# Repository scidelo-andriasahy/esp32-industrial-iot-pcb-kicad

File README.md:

# Industrial ESP32 IoT Hardware & KiCad PCB Ecosystem (Fortico R&D)

> **Author:** Tsikomia Scidelo ANDRIASAHY — Embedded Hardware R&D at [Fortico](https://sitewebfortico.vercel.app/fr)  
> **Live Project Showcase:** [https://scidelo-andriasahy.github.io/?project=5](https://scidelo-andriasahy.github.io/?project=5)

## Four Industrial Embedded Systems Included
1. **SMART_COUNT Industrial Counter PCB:** `ESP32` driving 4 cascaded `74HC595` shift registers + 4 seven-segment displays, ultrasonic object detection, and MQTT reporting.
2. **Automated Smart Incubator PCB:** MOSFET PID thermal loop, DHT22 hygrometry, NEMA 17 egg turning (`DRV8825`), `DS3231` RTC, and 12V/Battery automatic failover.
3. **Multi-Module Fleet Telematics IoT Box:** `ESP32` + `SIM7600` 4G LTE modem + NEO-6M GPS + RFID driver authentication + offline microSD buffering + security relay.
4. **Remote Operator HMI Terminal:** SSD1306 OLED, rotary encoder, and bidirectional `ESP-NOW` / `MQTT` telemetry for power converters.

## Repository Structure
```text
├── hardware/
│   ├── smart_count_kicad/      # Complete KiCad schematic & PCB layout for SMART_COUNT
│   └── smart_incubator_kicad/  # Complete KiCad schematic & PCB layout for Smart Incubator
├── docs/                       # ERC-verified PDF schematics & full functional/firmware specs
└── media/                      # 3D PCB renders & schematic previews
```

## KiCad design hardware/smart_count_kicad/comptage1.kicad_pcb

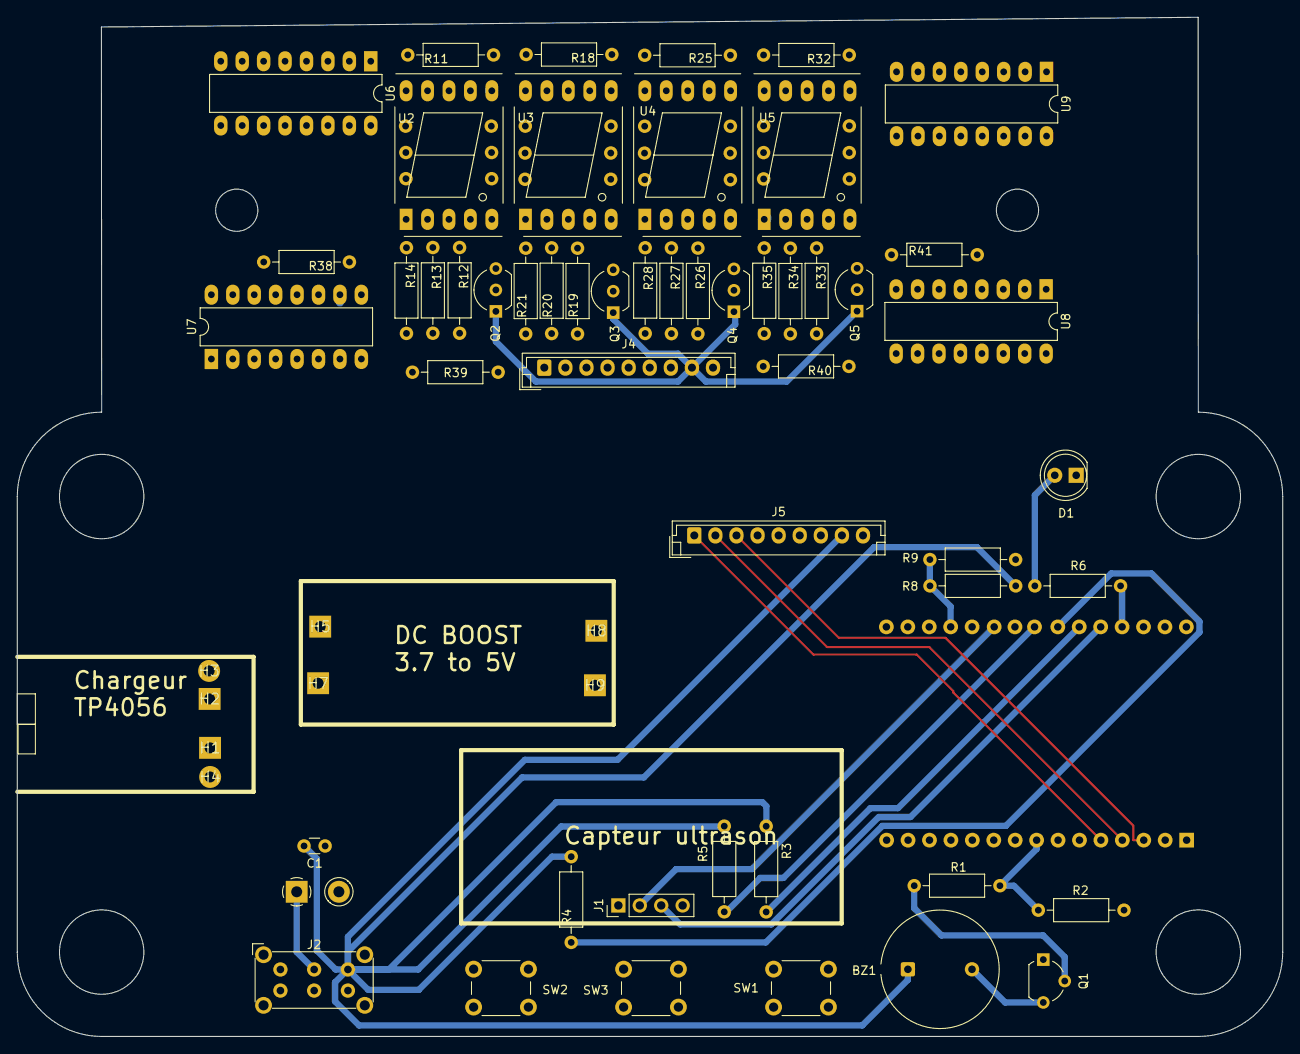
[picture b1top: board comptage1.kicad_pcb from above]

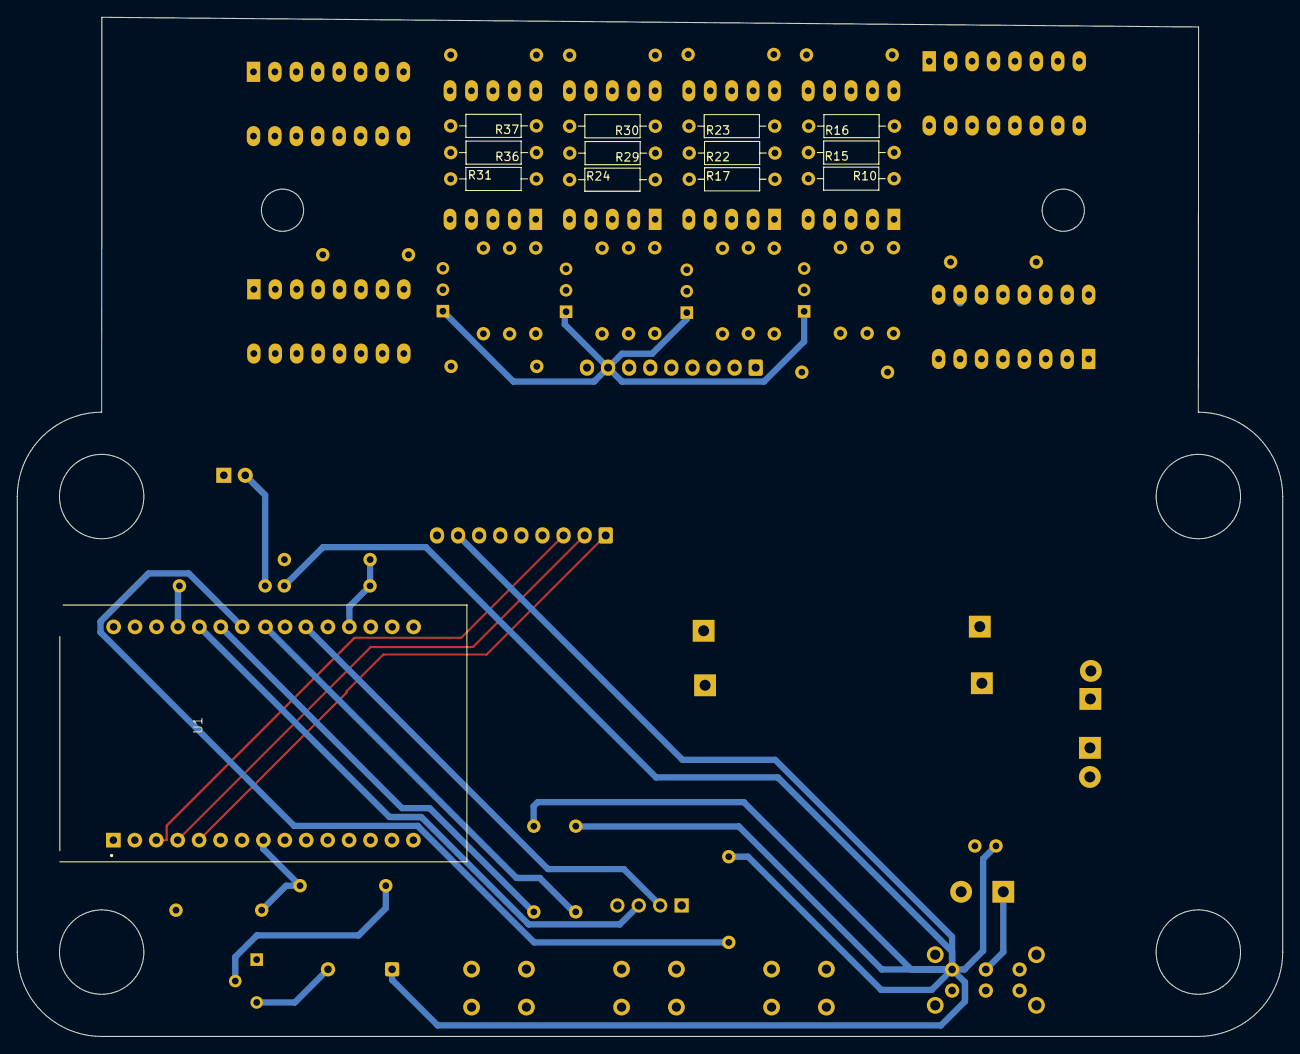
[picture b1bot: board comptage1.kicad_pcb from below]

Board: 2 copper layers, 150.0 x 120.8 mm, 73 parts (13 on the bottom side), 101 nets.

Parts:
BZ1: Buzzer; Indicator_PUI_AI-1440-TWT-24V-2-R
C1: 100nf; C_Disc_D3.0mm_W1.6mm_P2.50mm
D1: Alim; LED_D5.0mm
H1, H2, H3, H4, H5, H7, H8, H9: (no value)
J1: Conn_01x06; PinHeader_1x04_P2.54mm_Vertical
J2: Intérrupteur; SW_E-Switch_EG2219_DPDT_Angled
J3: Source; TerminalBlock_Phoenix_MKDS-1,5-2_1x02_P5.00mm_Horizontal
J4, J5: Conn_01x04; JST_EH_B9B-EH-A_1x09_P2.50mm_Vertical
Q1: 2SC1941; TO-92L_Wide
Q2, Q3, Q4, Q5: PNP; TO-92_Inline_Wide
R1, R38, R39, R40, R41: 330; R_Axial_DIN0207_L6.3mm_D2.5mm_P10.16mm_Horizontal
R2: 10ΚΩ; R_Axial_DIN0207_L6.3mm_D2.5mm_P10.16mm_Horizontal
R3, R4, R5: 10K; R_Axial_DIN0207_L6.3mm_D2.5mm_P10.16mm_Horizontal
R6, R10, R11, R12, R13, R14, R15, R16, R17, R18, R19, R20, R21, R22, R23, R24, R25, R26, R27, R28, R29, R30, R31, R32, R33, R34, R35, R36, R37: 32K; R_Axial_DIN0207_L6.3mm_D2.5mm_P10.16mm_Horizontal
R8, R9: 32KΩ; R_Axial_DIN0207_L6.3mm_D2.5mm_P10.16mm_Horizontal
SW1, SW2, SW3: SW_MEC_5G; SW_PUSH_6mm_H8mm
U1: ESP32-DEVKIT-V1; ESP32 DEVKIT V1
U2: Ecran 1; 7SegmentLED_LTS6760_LTS6780
U3: Ecran 2; 7SegmentLED_LTS6760_LTS6780
U4: Ecran 3; 7SegmentLED_LTS6760_LTS6780
U5: Ecran 4; 7SegmentLED_LTS6760_LTS6780
U6, U7, U8, U9: 74HC595; DIP-16_W7.62mm_LongPads

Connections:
/A1-: R10.2, U6.15 (QA)
/A2-: R17.2, U7.15 (QA)
/A3-: R24.2, U8.15 (QA)
/A4-: R31.2, U9.15 (QA)
/B1-: R11.2, U6.1 (QB)
/B2-: R18.2, U7.1 (QB)
/B3-: R25.2, U8.1 (QB)
/B4-: R32.2, U9.1 (QB)
/C1-: R12.2, U6.2 (QC)
/C2-: R19.2, U7.2 (QC)
/C3-: R26.2, U8.2 (QC)
/C4-: R33.2, U9.2 (QC)
/D1-: R13.2, U6.3 (QD)
/D2: J5.2, U1.4 (D2)
/D2-: R20.2, U7.3 (QD)
/D3-: R27.2, U8.3 (QD)
/D4: J5.1, U1.5 (D4)
/D4-: R34.2, U9.3 (QD)
/D5: R1.2, R2.2, U1.8 (D5)
/D12: R6.2, U1.27 (D12)
/D13: J5.4, U1.28 (D13)
/D14: J1.3, U1.26 (D14)
/D15: J5.3, U1.3 (D15)
/D21: J5.7, U1.11 (D21)
/D22: J5.6, U1.14 (D22)
/D23: J5.5, U1.15 (D23)
/D25: R5.2, U1.23 (D25)
/D26: R4.2, U1.24 (D26)
/D27: R3.2, U1.25 (D27)
/D32: J1.2, U1.21 (D32)
/D34: R8.2, R9.1, U1.19 (D34)
/DA2: J4.2, R39.2
/DA4: J4.1, R38.2
/DA13: J4.4, R41.2
/DA15: J4.3, R40.2
/DA21: J4.7, U6.12 (RCLK), U7.12 (RCLK), U8.12 (RCLK), U9.12 (RCLK)
/DA22: J4.6, U6.11 (SRCLK), U7.11 (SRCLK), U8.11 (SRCLK), U9.11 (SRCLK)
/DA23: J4.5, U6.14 (SER)
/DP1: U2.5 (DP), U6.7 (QH)
/DP2: U3.5 (DP), U7.7 (QH)
/DP3: U4.5 (DP), U8.7 (QH)
/DP4: U5.5 (DP), U9.7 (QH)
/E1-: R14.2, U6.4 (QE)
/E2-: R21.2, U7.4 (QE)
/E3-: R28.2, U8.4 (QE)
/E4-: R35.2, U9.4 (QE)
/F1-: R15.2, U6.5 (QF)
/F2-: R22.2, U7.5 (QF)
/F3-: R29.2, U8.5 (QF)
/F4-: R36.2, U9.5 (QF)
/G1-: R16.2, U6.6 (QG)
/G2-: R23.2, U7.6 (QG)
/G3-: R30.2, U8.6 (QG)
/G4-: R37.2, U9.6 (QG)
/GND1: J4.9, U6.8 (GND), U6.13 (~OE), U7.8 (GND), U7.13 (~OE), U8.8 (GND), U8.13 (~OE), U9.8 (GND), U9.13 (~OE)
/VCC1: J4.8, Q2.1 (C), Q3.1 (C), Q4.1 (C), Q5.1 (C), U6.10 (~SRCLR), U6.16 (VCC), U7.10 (~SRCLR), U7.16 (VCC), U8.10 (~SRCLR), U8.16 (VCC), U9.10 (~SRCLR), U9.16 (VCC)
GND: C1.1, D1.1 (K), J1.1, J3.2, J5.9, Q1.1 (E), R2.1, R9.2, SW1.2, SW2.2, SW3.2, U1.2 (GND), U1.29 (GND)
unnamed: BZ1.2 (+), Q1.2 (C)
unnamed: D1.2 (A), R6.1
unnamed: J2.2, J3.1
unnamed: Q1.3 (B), R1.1
unnamed: Q2.2 (B), R38.1
unnamed: Q2.3 (E), U2.3 (CC), U2.8 (CC)
unnamed: Q3.2 (B), R39.1
unnamed: Q3.3 (E), U3.3 (CC), U3.8 (CC)
unnamed: Q4.2 (B), R40.1
unnamed: Q4.3 (E), U4.3 (CC), U4.8 (CC)
unnamed: Q5.2 (B), R41.1
unnamed: Q5.3 (E), U5.3 (CC), U5.8 (CC)
unnamed: R10.1, U2.7 (A)
unnamed: R11.1, U2.6 (B)
unnamed: R12.1, U2.4 (C)
unnamed: R13.1, U2.2 (D)
unnamed: R14.1, U2.1 (E)
unnamed: R15.1, U2.9 (F)
unnamed: R16.1, U2.10 (G)
unnamed: R17.1, U3.7 (A)
unnamed: R18.1, U3.6 (B)
unnamed: R19.1, U3.4 (C)
unnamed: R20.1, U3.2 (D)
unnamed: R21.1, U3.1 (E)
unnamed: R22.1, U3.9 (F)
unnamed: R23.1, U3.10 (G)
unnamed: R24.1, U4.7 (A)
unnamed: R25.1, U4.6 (B)
unnamed: R26.1, U4.4 (C)
unnamed: R27.1, U4.2 (D)
unnamed: R28.1, U4.1 (E)
unnamed: R29.1, U4.9 (F)
unnamed: R30.1, U4.10 (G)
unnamed: R31.1, U5.7 (A)
unnamed: R32.1, U5.6 (B)
unnamed: R33.1, U5.4 (C)
unnamed: R34.1, U5.2 (D)
unnamed: R35.1, U5.1 (E)
unnamed: R36.1, U5.9 (F)
unnamed: R37.1, U5.10 (G)
unnamed: U6.9 (QH'), U7.14 (SER)
unnamed: U7.9 (QH'), U8.14 (SER)
unnamed: U8.9 (QH'), U9.14 (SER)
VCC: BZ1.1 (-), C1.2, J1.4, J2.3, J5.8, R3.1, R4.1, R5.1, R8.1, U1.30 (VIN)
